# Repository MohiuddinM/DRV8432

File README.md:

This is a DRV8432 driver board. Can be used to control electrical buggy or large RC cars.
Maximum continuous current should be less than 3A for heatsinkless operation.

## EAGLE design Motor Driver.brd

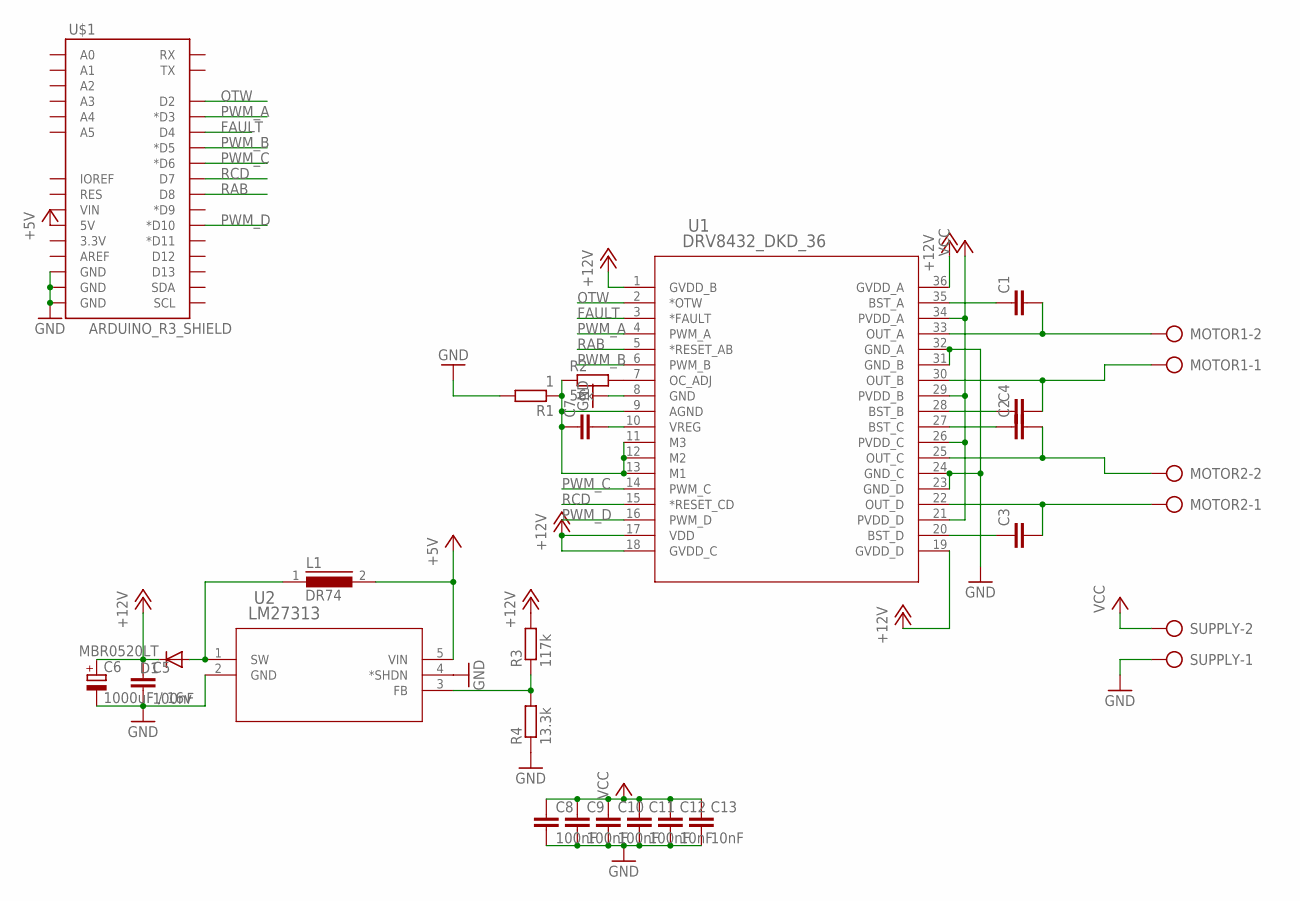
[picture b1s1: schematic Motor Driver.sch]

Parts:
C1, C2, C3, C4: C-EUC0402K; C0402K
C5, C8, C9, C10, C11: 100nF; C0805K
C6: 1000uF / 16v; B45181B
C7: C-EUC0805K; C0805K
C12, C13: 10nF; C0805K
D1: MBR0520LT; SOD123
L1: DR74
MOTOR1, MOTOR2: AK300/2
R1: 1; M0805
R2: 56k; M0805
R3: 117k; R0805
R4: 13.3k; R0805
SUPPLY: AK300/2
U1: DRV8432_DKD_36; DKD36
U2: LM27313; MF05A
U$1: ARDUINO_R3_SHIELD; UNO_R3_SHIELD

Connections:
+5V: L1.2, U2.5 (VIN), U$1.5V
+12V: C5.1, C6.+, D1.C, R3.2, U1.1 (GVDD_B), U1.17 (VDD), U1.18 (GVDD_C), U1.19 (GVDD_D), U1.36 (GVDD_A)
FAULT: U1.3 (*FAULT), U$1.D4
GND: C5.2, C6.-, C8.2, C9.2, C10.2, C11.2, C12.2, C13.2, R1.2, R4.1, SUPPLY.1, U1.8 (GND), U1.23 (GND_D), U1.24 (GND_C), U1.31 (GND_B), U1.32 (GND_A), U2.2 (GND), U2.4 (*SHDN), U$1.GND@0 (GND), U$1.GND@1 (GND), U$1.GND@2 (GND)
unnamed: C1.1, U1.35 (BST_A)
unnamed: C2.1, U1.27 (BST_C)
unnamed: C3.1, U1.20 (BST_D)
unnamed: C4.1, U1.28 (BST_B)
unnamed: C1.2, MOTOR1.2, U1.33 (OUT_A)
unnamed: C4.2, MOTOR1.1, U1.30 (OUT_B)
unnamed: C2.2, MOTOR2.2, U1.25 (OUT_C)
unnamed: C3.2, MOTOR2.1, U1.22 (OUT_D)
unnamed: C7.2, U1.10 (VREG)
unnamed: D1.A, L1.1, U2.1 (SW)
unnamed: R3.1, R4.2, U2.3 (FB)
unnamed: R2.2, U1.7 (OC_ADJ)
unnamed: C7.1, R1.1, R2.1, U1.9 (AGND), U1.11 (M3), U1.12 (M2), U1.13 (M1)
OTW: U1.2 (*OTW), U$1.D2
PWM_A: U1.4 (PWM_A), U$1.D3 (*D3)
PWM_B: U1.6 (PWM_B), U$1.D5 (*D5)
PWM_C: U1.14 (PWM_C), U$1.D6 (*D6)
PWM_D: U1.16 (PWM_D), U$1.D10 (*D10)
RAB: U1.5 (*RESET_AB), U$1.D8
RCD: U1.15 (*RESET_CD), U$1.D7
VCC: C8.1, C9.1, C10.1, C11.1, C12.1, C13.1, SUPPLY.2, U1.21 (PVDD_D), U1.26 (PVDD_C), U1.29 (PVDD_B), U1.34 (PVDD_A)

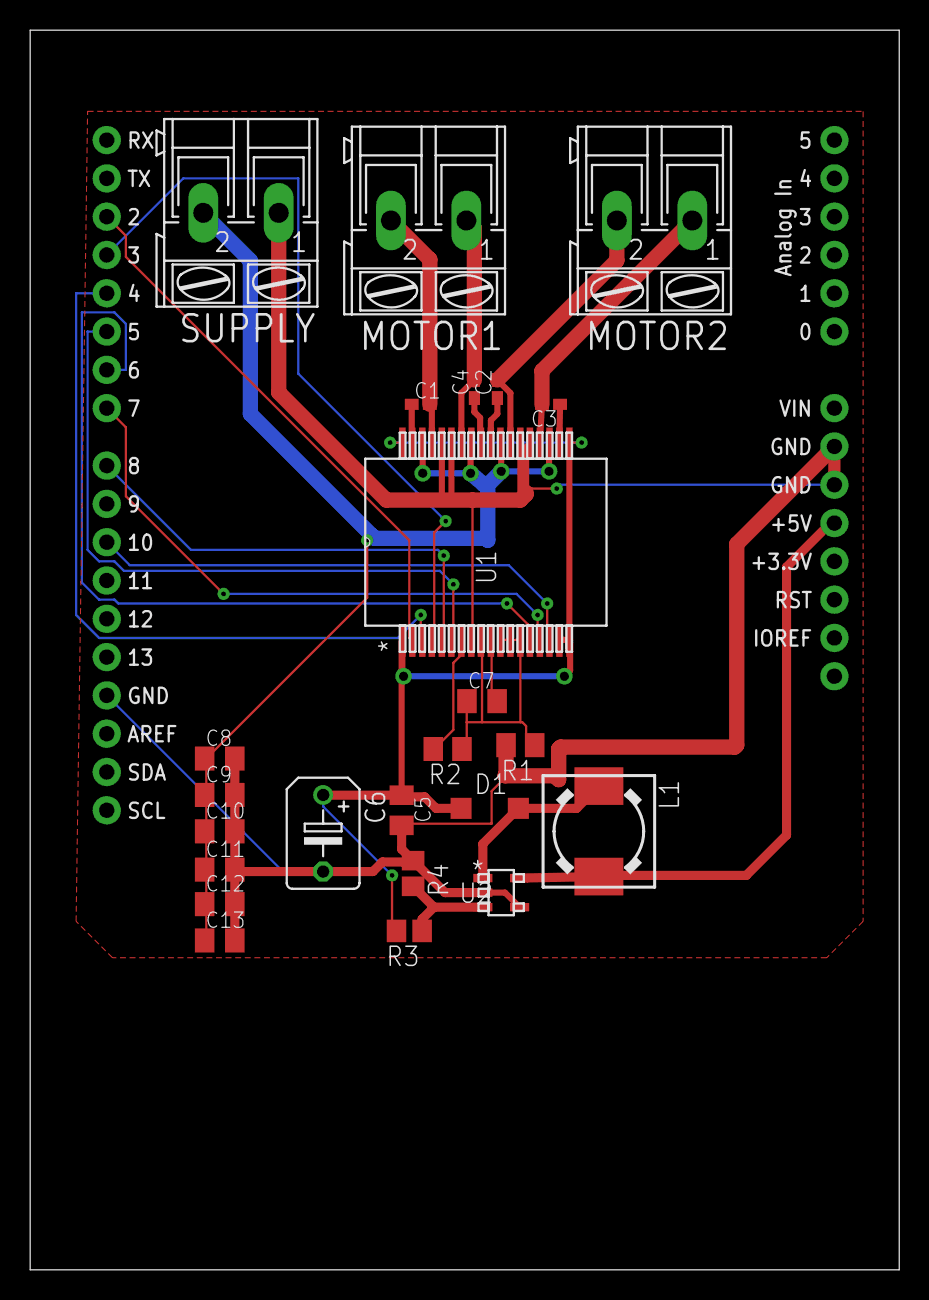
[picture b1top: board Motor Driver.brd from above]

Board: 2 copper layers, 57.6 x 82.2 mm, 25 parts (0 on the bottom side), 25 nets.

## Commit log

2014-05-18 Uploading Board
2016-08-02 Typo Fix

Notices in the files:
parts and their libraries:
SparkFun-Boards: Licensing: CC v3.0 Share-Alike You are welcome to use this library for commercial purposes.
